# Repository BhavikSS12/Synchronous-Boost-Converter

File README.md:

# 5V to 10–20V, 20W Synchronous Boost Converter

A fully designed and built **synchronous boost converter** that steps up a 5V input to an adjustable 10–20V output at up to 20W. The design implements both **open-loop** and **closed-loop** control modes on a single hardware platform, with a dedicated MC34063-based auxiliary supply that solves the classic 5V bootstrap deadlock.

---

## Features

- **Input:** 5V (USB or regulated supply, ≥5A source recommended)
- **Output:** Adjustable 10V–20V, up to 20W (1A at 20V)
- **Synchronous rectification** using dual N-channel MOSFETs (IRF3205)
- **PWM control** via SG3525A with open-loop and closed-loop modes selectable via switch
- **High-side + low-side gate drive** using IR2110 with bootstrap circuit
- **Auxiliary 12V control supply** generated from 5V input using MC34063 — eliminates startup deadlock
- **Hand-wound toroidal inductor** (33 µH, 19 turns) with energy-based core selection

---

## System Architecture

The design is split into two functional blocks:

**1. Auxiliary Control Supply (MC34063)**
Boosts 5V → ~12V to power the SG3525A and IR2110. This solves the startup deadlock — the SG3525A requires >5V to operate and cannot self-start from the 5V input rail alone.

**2. Main Synchronous Boost Stage (SG3525A + IR2110 + IRF3205)**
- SG3525A generates PWM and provides oscillator, error amplifier, soft-start, and reference
- IR2110 drives both low-side (M1) and floating high-side (M2) N-channel MOSFETs via bootstrap
- Two IRF3205 MOSFETs perform synchronous energy transfer from inductor to output

---

## Key Design Parameters

| Parameter | Value |
|---|---|
| Input Voltage | 5V |
| Output Voltage | 10V – 20V (adjustable) |
| Max Output Power | 20W |
| Max Output Current | 1A (at 20V) |
| Max Input Current | ~4.7A (at 85% efficiency) |
| Max Duty Cycle | 75% (at Vout = 20V) |
| Switching Frequency | 100 kHz |
| Peak Inductor Current | ~5.3A |

---

## Design Calculations

### Duty Cycle

At maximum output (20V):

$$D = 1 - \frac{V_{in}}{V_{out}} = 1 - \frac{5}{20} = 0.75$$

### Input Current (at 85% efficiency)

$$I_{in} = \frac{P_{out}}{\eta \cdot V_{in}} = \frac{20}{0.85 \times 5} \approx 4.7\text{ A}$$

### Inductor Value (25% ripple target)

$$\Delta I_L = 0.25 \times 4.7 = 1.18\text{ A}$$

$$L = \frac{V_{in} \cdot D}{f_{sw} \cdot \Delta I_L} = \frac{5 \times 0.75}{100000 \times 1.18} \approx 31.8\text{ µH} \rightarrow \textbf{33 µH}$$

### Peak Inductor Current

$$I_{peak} = I_{in} + \frac{\Delta I_L}{2} = 4.7 + \frac{1.18}{2} \approx 5.3\text{ A}$$

Inductor saturation rating chosen: **≥ 6A**

### Output Capacitor

$$C_{out} = \frac{I_{out} \cdot D}{f_{sw} \cdot \Delta V_{out}} = \frac{1 \times 0.75}{100000 \times 0.2} = 37.5\text{ µF} \rightarrow \textbf{2 × 47 µF (parallel)}$$

---

## Auxiliary Supply — MC34063 Design (5V → 12V)

The MC34063 auxiliary stage is independently designed and verified using the official ON Semiconductor datasheet equations.

### Design Parameters

| Parameter | Value |
|---|---|
| Input | 5V |
| Output | ~12V |
| Inductor | 47µH (CDRH104R, ferrite, 1.9A rated, DCR = 128mΩ) |
| Diode | 1N5819 Schottky |
| Rsc | 2× 0.47Ω in parallel = 0.235Ω |
| Peak Switch Current (Ipk) | 1.277A |
| Switching Frequency | ~43 kHz |
| Max Output Current | ~224mA |

### MC34063 Auxiliary Supply Calculations

**ton/toff ratio** (from voltage conversion ratio):

$$\frac{t_{on}}{t_{off}} = \frac{V_{out} + V_f - V_{in}}{V_{in} - V_{sat}} = \frac{12 + 0.4 - 5}{5 - 1} = 1.85$$

**Peak current** (set by Rsc):

$$I_{pk} = \frac{0.3}{R_{sc}} = \frac{0.3}{0.235} = 1.277\text{ A}$$

**ON-time** (from inductor current ramp):

$$t_{on} = \frac{I_{pk} \times L}{V_{in} - V_{sat}} = \frac{1.277 \times 47 \times 10^{-6}}{4} = 15.0\text{ µs}$$

**Timing capacitor** (datasheet equation):

$$C_t = 4.0 \times 10^{-5} \times t_{on} = 4.0 \times 10^{-5} \times 15.0 \times 10^{-6} = 600\text{ pF} \rightarrow \textbf{680 pF (standard)}$$

**Output voltage** (feedback divider):

$$V_{out} = 1.25 \times \left(1 + \frac{R_2}{R_1}\right) = 1.25 \times \left(1 + \frac{19000}{2200}\right) = 12.0\text{ V}$$

### MC34063 Component List

| Component | Value | Notes |
|---|---|---|
| IC | MC34063A | DIP-8 |
| L1 | 47µH — CDRH104R | Ferrite, 1.9A rated, DCR = 128mΩ |
| D1 | 1N5819 | Schottky rectifier |
| Rsc | 2× 0.47Ω in parallel | 0.235Ω effective |
| Ct | 680pF ceramic | Sets fsw ≈ 43kHz |
| Cin | 100µF / 10V | Electrolytic, close to Pin 6 |
| Cout | 100µF / 25V | Electrolytic, across 12V output |
| R1 | 2.2kΩ | Pin 5 to GND |
| R2 | 18kΩ + 1kΩ in series (= 19kΩ) | Vout to Pin 5 |
| R4 | 100Ω | Pin 8 to Vin — do not omit |

---

## Toroidal Core Inductor — Design & Winding

### Core Selection via Energy Method

$$E = \frac{1}{2} L I_{peak}^2 = \frac{1}{2} \times 33 \times 10^{-6} \times (5.3)^2 \approx 463\text{ µJ}$$

The core's energy handling capability was verified to exceed this value with adequate margin before finalising the core.

### Turn Count

$$N = \sqrt{\frac{L}{A_L}}$$

For the selected core with AL ≈ 135 nH/turn²:

$$N = \sqrt{\frac{33 \times 10^{-6}}{135 \times 10^{-9}}} \approx 15.6 \rightarrow \textbf{19 turns (with margin)}$$

19 turns were wound to ensure the inductance target is met with headroom, accounting for winding geometry and practical AL variation.

**Wire:** AWG 16 magnet wire — rated for RMS inductor current with acceptable temperature rise.

---

## Component Selection

### Main Power Stage

| Component | Value / Part | Reason |
|---|---|---|
| M1, M2 | IRF3205 | Low Rds(on), high current for 5V-input high-current design |
| PWM IC | SG3525A | Built-in oscillator, error amplifier, soft-start, and shutdown |
| Gate Driver | IR2110 | Floating high-side + low-side N-channel MOSFET drive |
| Main Inductor | 33µH, 26T toroid, ≥6A sat | Meets ripple and peak current requirement |
| Output Capacitor | 2× 47µF / 35V low-ESR | Ripple reduction and output energy storage |
| Input Capacitor | 100µF / 10V + 10µF ceramic | Reduces input droop and HF noise |
| Bootstrap Capacitor | 100nF / 50V | Required by IR2110 high-side drive |
| Bootstrap Diode | UF4007 | Fast recovery diode for bootstrap charging path |
| Gate Resistors | 10Ω | Current limiting and ringing suppression |

### Auxiliary Supply (MC34063)

| Component | Value / Part | Reason |
|---|---|---|
| IC | MC34063A | Step-up regulator, operates directly from 5V |
| Inductor | 47µH — CDRH104R | Ferrite core, low DCR (128mΩ), 1.9A rated |
| Diode | 1N5819 | Low forward-drop Schottky rectifier |
| Rsc | 2× 0.47Ω in parallel | Sets Ipk = 1.277A; within 1.5A IC limit |
| Timing Capacitor | 680pF | Sets fsw ≈ 43kHz per datasheet equation |
| Output Capacitor | 100µF / 25V | Stabilises 12V control rail |
| R1 | 2.2kΩ | Bottom of feedback divider |
| R2 | 18kΩ + 1kΩ in series | Sets output to exactly 12.0V |
| R4 (driver) | 100Ω | Base current limiting for Pin 8 internal driver |

---

## Control Modes

A mode-select switch routes either signal to the SG3525A control input:

**Open-loop mode:** VR2 potentiometer divides the SG3525A's internal 5.1V reference to produce a manually adjustable duty cycle. Output voltage varies without automatic correction.

**Closed-loop mode:** VR1 potentiometer sets the regulation setpoint. The output is divided down and compared with the 5.1V reference through the SG3525A error amplifier. Duty cycle automatically adjusts to maintain the set output voltage.

---

## Schematics

| File | Description |
|---|---|
| `schematic and PCB layout/full_schematic.pdf` | Complete circuit schematic |
| `schematic and PCB layout/auxiliary_supply_mc34063.png` | MC34063 5V → 12V auxiliary stage |
| `schematic and PCB layout/main_boost_stage.png` | SG3525A + IR2110 + IRF3205 power stage |

---

## Testing Procedure

### Phase 1 — Visual Check (Before Power-On)

- Verify IC orientation — Pin 1 dot matches schematic
- Check 1N5819 polarity — stripe (cathode) faces Vout
- Check electrolytic capacitor polarity (Cin and Cout)
- Confirm both 0.47Ω Rsc resistors soldered in parallel between Pin 7 and Pin 6
- Measure Rsc with multimeter → should read ~0.23–0.25Ω

### Phase 2 — Auxiliary Supply First

1. Apply 5V to input with no main stage load
2. Measure MC34063 output → should read **11.8–12.2V**
3. Probe Pin 3 (Ct) with oscilloscope → ~43kHz sawtooth

### Phase 3 — Main Stage Bring-Up (Current-Limited Supply)

1. Set bench supply current limit to **1A initially**
2. Open-loop mode, start at minimum duty (VR2 fully wound down)
3. Gradually increase duty — monitor switch node for ringing
4. Verify IR2110 HO/LO gate signals and confirm dead time is present
5. Increase load progressively to full 20W

### Phase 4 — Full Load Verification

| Measurement | Expected Value |
|---|---|
| Vout (no load) | 10–20V adjustable |
| Vout (full load, 20W) | Stable within ±5% |
| Input current at 20W | ~4.7A |
| Output ripple | < 200mV peak-to-peak |
| Efficiency | 75–85% |
| MOSFET temperature at 20W | < 60°C (add heatsink if higher) |

---

## Test Results

See [`results/measurements.md`](results/measurements.md) for full tabulated results.

> **Note:** Results will be populated after once tested with proper testing setup.

---

## Build Notes and Cautions

- **Switch node layout is critical.** Keep M1 drain, M2 source, inductor connection, and IR2110 VS pin in a tight loop. Excessive PCB area causes ringing and EMI.
- **Always bring up the MC34063 auxiliary rail first.** Confirm ~12V on the control rail before enabling the main switching stage.
- **Use a current-limited bench supply** for initial main stage testing. Start at reduced duty in open-loop before enabling closed-loop.
- **Verify inductor saturation margin.** At 5.3A peak, use an inductor rated ≥6A. Saturation causes uncontrolled current spikes that can destroy the MOSFETs instantly.
- **Check thermal rise at 20W.** Conduction and switching losses at 4.7A input current are significant. Heatsinking of IRF3205 may be required.
- **Do not omit R4 (100Ω) on MC34063 Pin 8.** Without it, the internal driver transistor cannot be properly biased at 5V Vin.

---

## Known Limitations

- No dedicated overcurrent protection on the main boost stage — rely on bench supply current limiting during testing
- Soft-start provided by SG3525A but not independently tuned; may need adjustment for different load profiles
- Closed-loop compensation network not fully optimised — transient response may show overshoot under step-load changes

---

## Repo Structure

```
Boost-converter-5v-20v/
├── README.md
├── docs/
│   ├── design_report.pdf
│   ├── calculations.md
│   └── energy_core_selection.md
├── schematic and PCB layout/
│   ├── full_schematic.pdf
│   ├── auxiliary_supply_mc34063.png
│   └── main_boost_stage.png
├── DesignFiles/
│   ├── BOM
│   ├── EAGLECAD Project file
│   ├── EAGLECAD schematic file
│   ├── EAGLECAD BRD file
│   ├── Gerber files
│   └── Drill fies
├── Images/
│   ├── board_top.jpg
│   ├── board_bottom.jpg
│   ├── inductor_wound.jpg
│   ├── test_setup.jpg
│   ├── waveform_gate_drive.jpg
│   ├── waveform_switch_node.jpg
│   └── output_voltage_regulation.jpg
└── results/
    └── measurements.md
```

---

## References

- SG3525A Datasheet — Texas Instruments
- IR2110 Datasheet — Infineon (formerly International Rectifier)
- IRF3205 Datasheet — Infineon
- MC34063A Datasheet — ON Semiconductor / onsemi
- Mohan, Undeland & Robbins — *Power Electronics: Converters, Applications, and Design*

---

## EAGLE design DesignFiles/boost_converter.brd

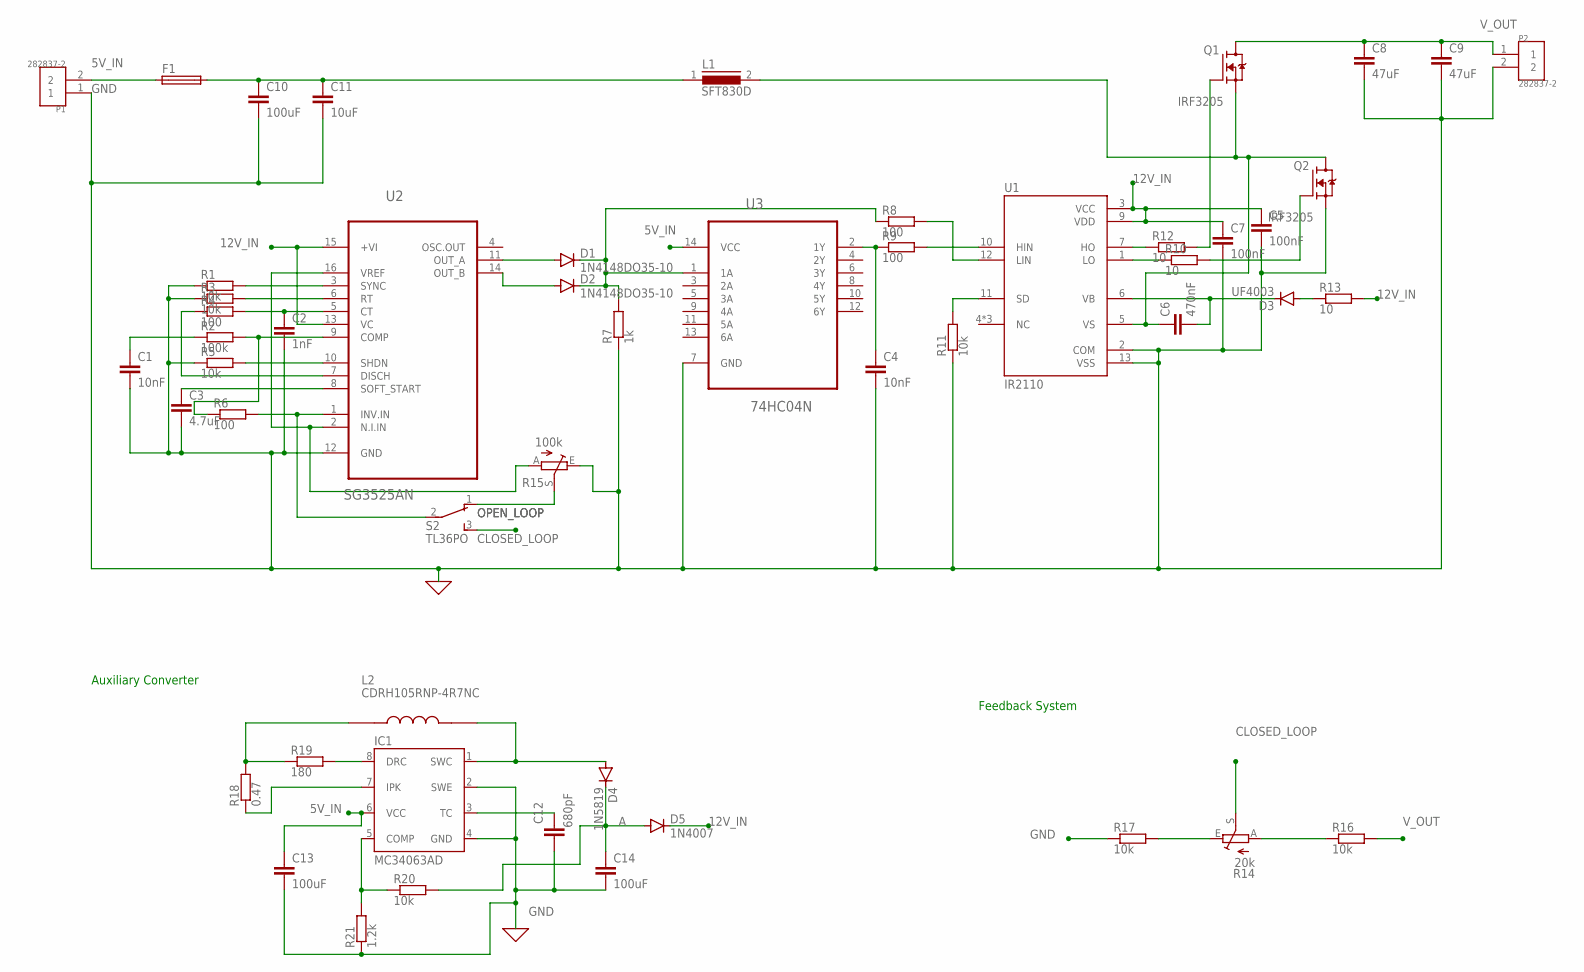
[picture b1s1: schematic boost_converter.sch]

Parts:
C1, C4: 10nF; C2.5-3
C2: 1nF; C2.5-3
C3: 4.7uF; C2.5-5
C5, C7: 100nF; C2.5-3
C6: 470nF; C2.5-3
C8, C9: 47uF; C2.5-5
C10, C13, C14: 100uF; C2.5-5
C11: 10uF; C2.5-5
C12: 680pF; C2.5-3
D1, D2: 1N4148DO35-10; DO35-10
D3: UF4003; DO41-10
D4: 1N5819; DO41-10
D5: 1N4007; DO41-10
F1: GSH15
IC1: MC34063AD; SO08
L1: SFT830D
L2: CDRH105RNP-4R7NC; IND_CDRH105RNP-4R7NC
P1, P2: 282837-2; TE_282837-2
Q1, Q2: IRF3205; TO254P1041X444X2933-3
R1, R3, R5, R11, R20: 10k; 0207/10
R2: 100k; 0207/10
R4, R6, R8, R9: 100; 0207/10
R7: 1k; 0207/10
R10, R12, R13: 10; 0207/10
R14: 20k; S64W
R15: 100k; S64W
R16, R17: 10k; 0309/10
R18: 0.47; 0207/10
R19: 180; 0207/10
R21: 1.2k; 0207/10
S2: TL36PO; TL3XPO
U1: IR2110; DIP762W45P254L2019H533Q14
U2: SG3525AN; DIP254P762X510-16
U3: 74HC04N; DIP254P762X420-14

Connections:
5V_IN: C10.1, C11.1, C13.1, F1.1, F1.2, IC1.6 (VCC), L1.1, P1.2, U3.14 (VCC)
12V_IN: C5.1, C7.1, D5.C, R13.2, U1.3 (VCC), U1.9 (VDD), U2.13 (VC), U2.15 (+VI)
A: C14.1, D4.C, D5.A, R20.2
CLOSED_LOOP: R14.S, S2.3 (S)
GND: C1.2, C2.2, C3.2, C4.2, C5.2, C7.2, C8.2, C9.2, C10.2, C11.2, C12.1, C13.2, C14.2, IC1.2 (SWE), IC1.4 (GND), P1.1, P2.2, Q2.3 (S), R1.1, R3.1, R5.1, R7.1, R11.1, R15.E, R17.1, R21.1, U1.2 (COM), U1.13 (VSS), U2.12 (GND), U3.7 (GND)
unnamed: R15.A, U2.2 (N.I.IN), U2.16 (VREF)
unnamed: R2.2, R6.1, U2.9 (COMP)
unnamed: C1.1, R2.1
unnamed: R3.2, U2.6 (RT)
unnamed: R1.2, U2.3 (SYNC)
unnamed: C2.1, R4.2, U2.5 (CT)
unnamed: R4.1, U2.7 (DISCH)
unnamed: D3.A, R13.1
unnamed: R5.2, U2.10 (SHDN)
unnamed: C3.1, U2.8 (SOFT_START)
unnamed: R6.2, S2.2, U2.1 (INV.IN)
unnamed: D2.A, U2.14 (OUT_B)
unnamed: D1.A, U2.11 (OUT_A)
unnamed: D1.C, D2.C, R7.2, R8.1, U3.1 (1A)
unnamed: R8.2, U1.12 (LIN)
unnamed: C4.1, R9.1, U3.2 (1Y)
unnamed: R9.2, U1.10 (HIN)
unnamed: R10.1, U1.1 (LO)
unnamed: IC1.8 (DRC), R19.2
unnamed: L2.1, R18.2, R19.1
unnamed: C6.1, L1.2, Q1.3 (S), Q2.2 (D), U1.5 (VS)
unnamed: C6.2, D3.C, U1.6 (VB)
unnamed: R11.2, U1.11 (SD)
unnamed: R12.1, U1.7 (HO)
unnamed: Q2.1 (G), R10.2
unnamed: Q1.1 (G), R12.2
unnamed: R14.A, R16.1
unnamed: R14.E, R17.2
unnamed: IC1.7 (IPK), R18.1
unnamed: IC1.5 (COMP), R20.1, R21.2
unnamed: C12.2, IC1.3 (TC)
unnamed: D4.A, IC1.1 (SWC), L2.2
OPEN_LOOP: R15.S, S2.1 (O)
V_OUT: C8.1, C9.1, P2.1, Q1.2 (D), R16.2

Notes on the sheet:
Feedback System
Auxiliary Converter

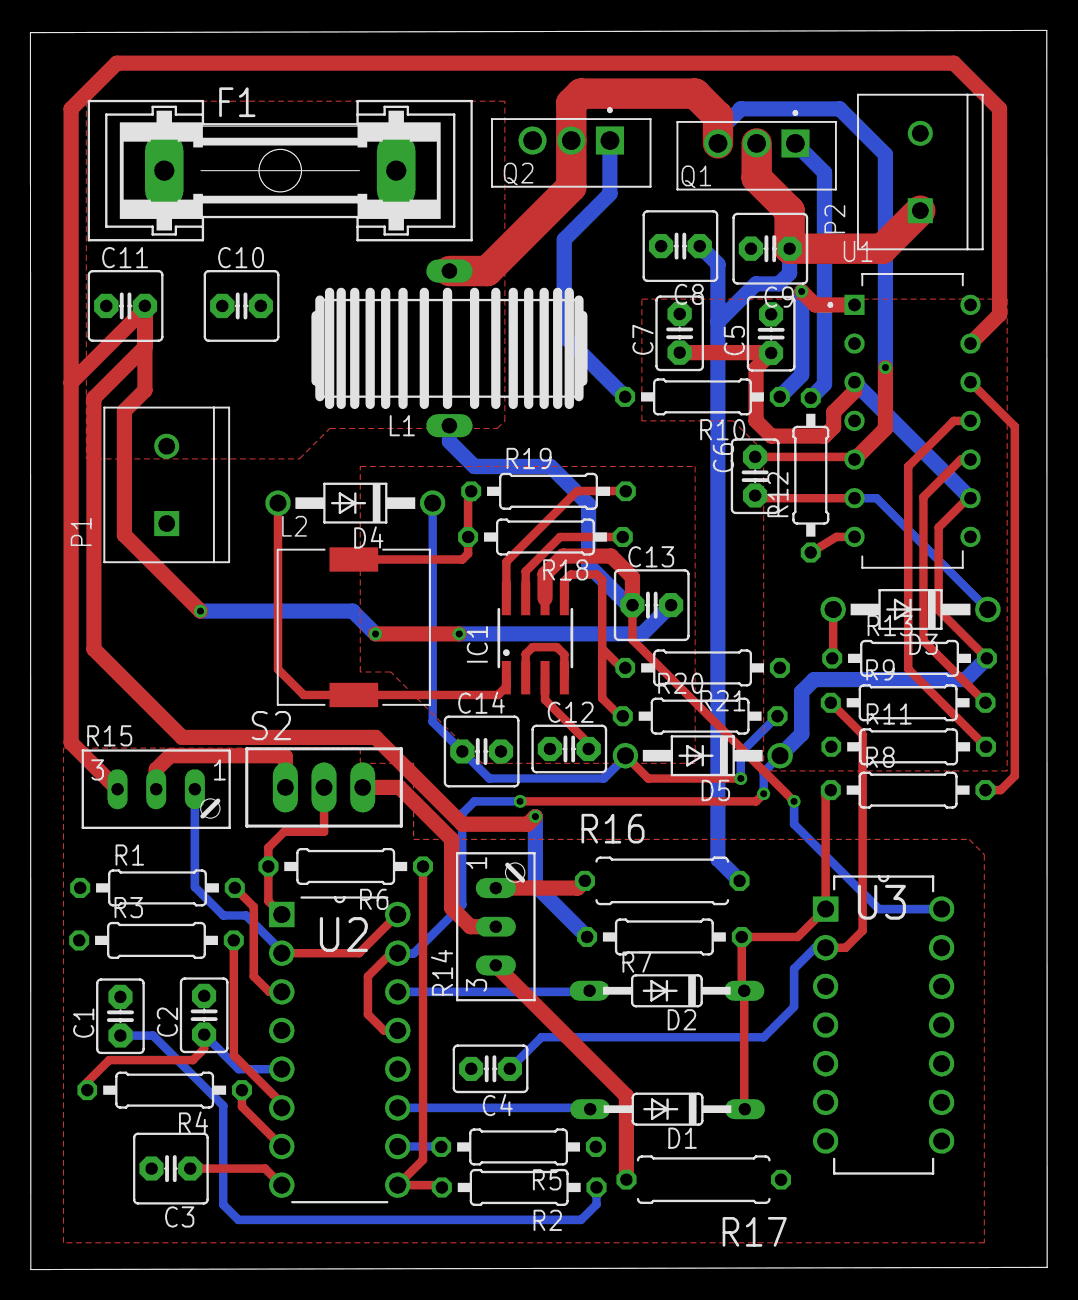
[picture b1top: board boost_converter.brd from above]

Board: 2 copper layers, 66.8 x 81.4 mm, 52 parts (0 on the bottom side), 39 nets.

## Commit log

2026-06-17 Schematic and BRD Files
2026-06-17 Schematic and BRD Files 2
2026-06-17 Calculation changes
2026-06-17 image added
2026-06-17 Results added
